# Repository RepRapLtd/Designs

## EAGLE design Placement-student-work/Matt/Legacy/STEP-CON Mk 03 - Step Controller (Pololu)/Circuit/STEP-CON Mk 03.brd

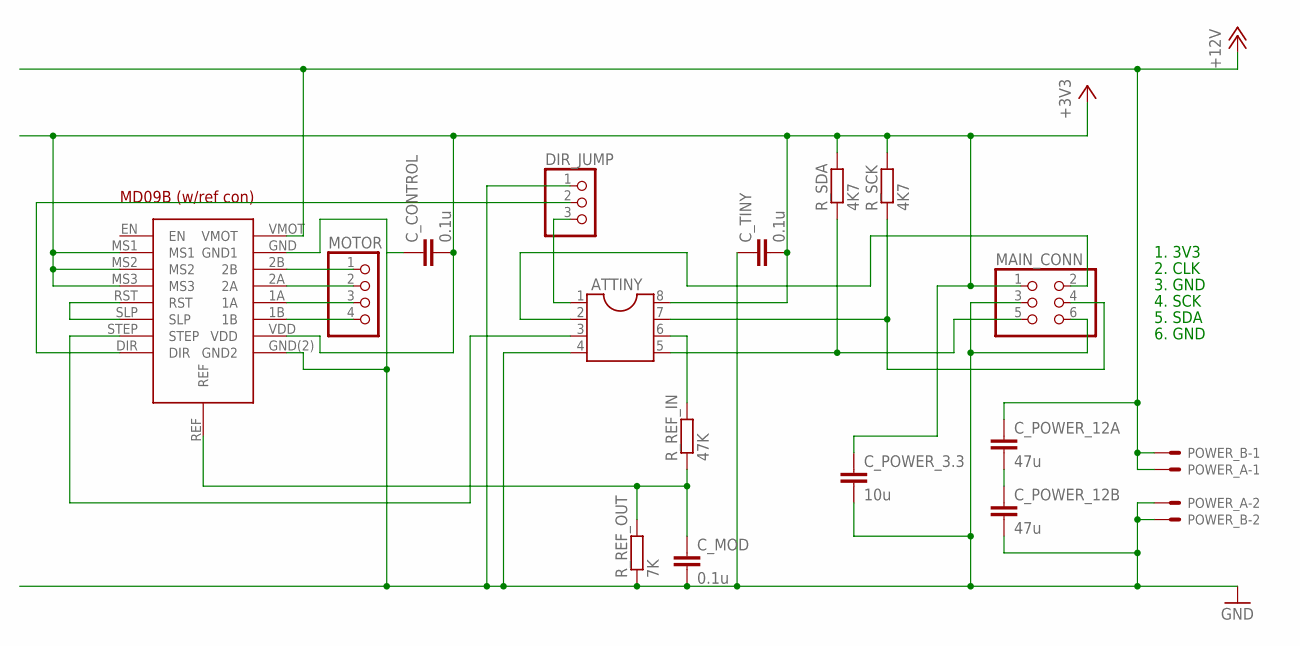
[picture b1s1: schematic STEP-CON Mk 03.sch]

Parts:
ATTINY: DIL8; DIL08
C_CONTROL: 0.1u; C1206
C_MOD: 0.1u; C1206
C_POWER_3.3: 10u; C1206
C_POWER_12A, C_POWER_12B: 47u; C1206
C_TINY: 0.1u; C1206
DIR_JUMP: PINHD-1X3; 1X03
MAIN_CONN: PINHD-2X3; 2X03
MOTOR: PINHD-1X4; 1X04
POWER_A: KK-156-2
POWER_B: KK-156-2
R_REF_IN: 47K; M0805
R_REF_OUT: 7K; M0805
R_SCK: 4K7; M0805
R_SDA: 4K7; M0805
U$1: MD09B_MOD_LP; MD90B_MOD_LP

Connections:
1A: MOTOR.3, U$1.1A
1B: MOTOR.4, U$1.1B
2A: MOTOR.2, U$1.2A
2B: MOTOR.1, U$1.2B
+3V3: ATTINY.8, C_CONTROL.2, C_POWER_3.3.1, C_TINY.2, MAIN_CONN.1, R_SCK.2, R_SDA.2, U$1.MS1, U$1.MS2, U$1.MS3, U$1.VDD
+12V: C_POWER_12A.1, POWER_A.1, POWER_B.1, U$1.VMOT
DIR: DIR_JUMP.2, U$1.DIR
GND: ATTINY.4, C_CONTROL.1, C_MOD.2, C_POWER_3.3.2, C_POWER_12B.2, C_TINY.1, DIR_JUMP.1, MAIN_CONN.3, MAIN_CONN.6, POWER_A.2, POWER_B.2, R_REF_OUT.1, U$1.GND (GND1), U$1.GND(2) (GND2)
unnamed: C_POWER_12A.2, C_POWER_12B.1
PWM: ATTINY.6, R_REF_IN.2
REF: C_MOD.1, R_REF_IN.1, R_REF_OUT.2, U$1.REF
RESET/DIR: ATTINY.1, DIR_JUMP.3
RST_SLP: U$1.RST, U$1.SLP
SCK: ATTINY.7, MAIN_CONN.4, R_SCK.1
SDA: ATTINY.5, MAIN_CONN.5, R_SDA.1
SKYCLOCK: ATTINY.2, MAIN_CONN.2
STEP: ATTINY.3, U$1.STEP

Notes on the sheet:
1. 3V3 2. CLK 3. GND 4. SCK 5. SDA 6. GND

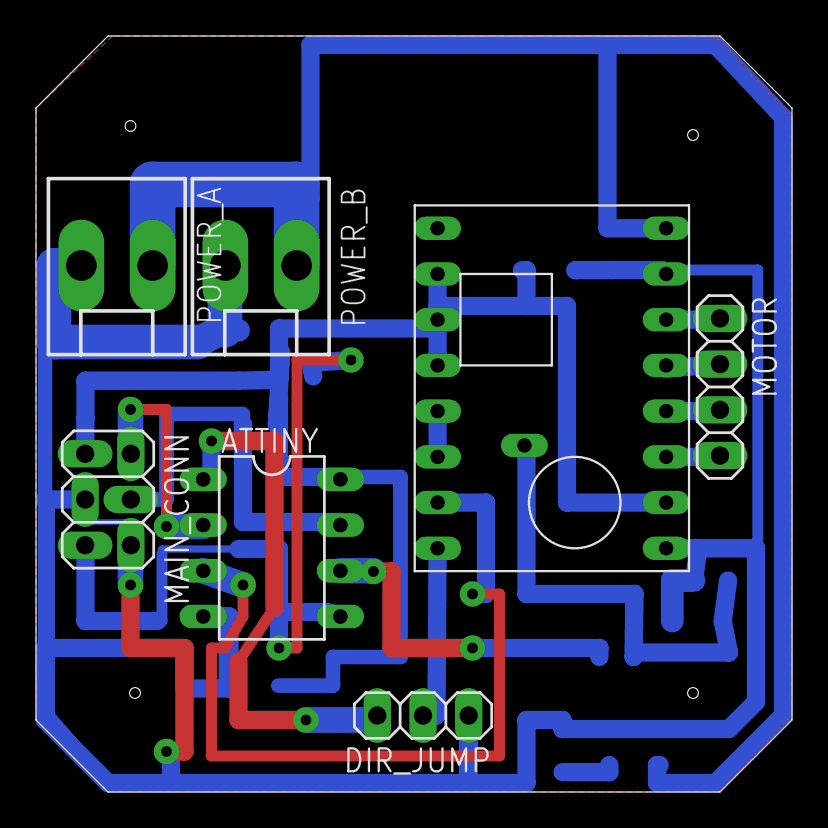
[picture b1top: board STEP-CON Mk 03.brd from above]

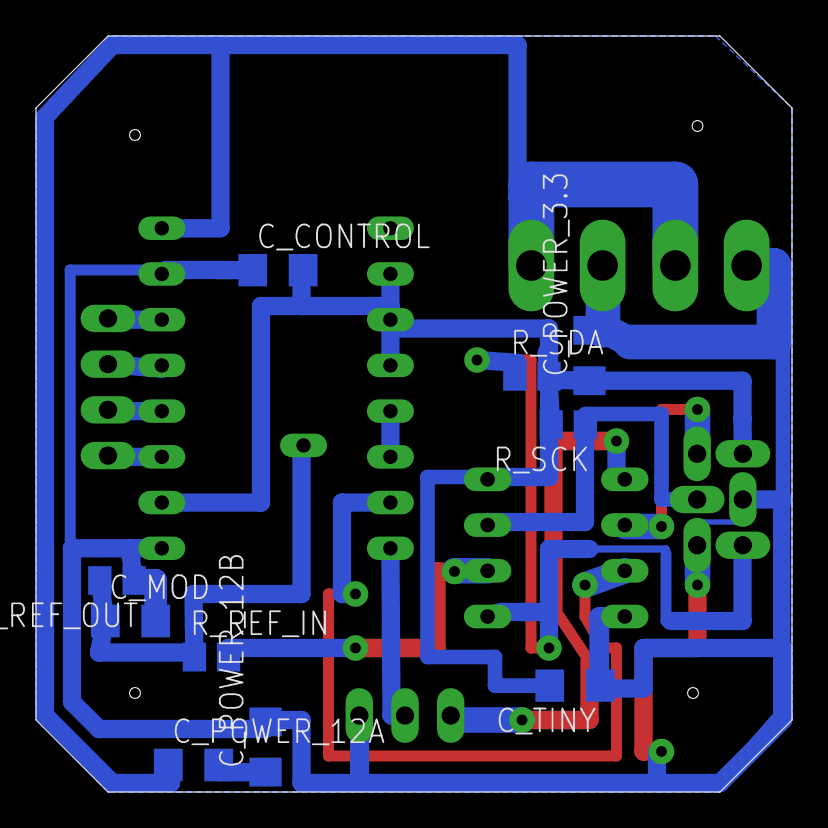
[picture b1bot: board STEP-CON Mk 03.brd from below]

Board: 2 copper layers, 42.0 x 42.0 mm, 17 parts (10 on the bottom side), 17 nets.

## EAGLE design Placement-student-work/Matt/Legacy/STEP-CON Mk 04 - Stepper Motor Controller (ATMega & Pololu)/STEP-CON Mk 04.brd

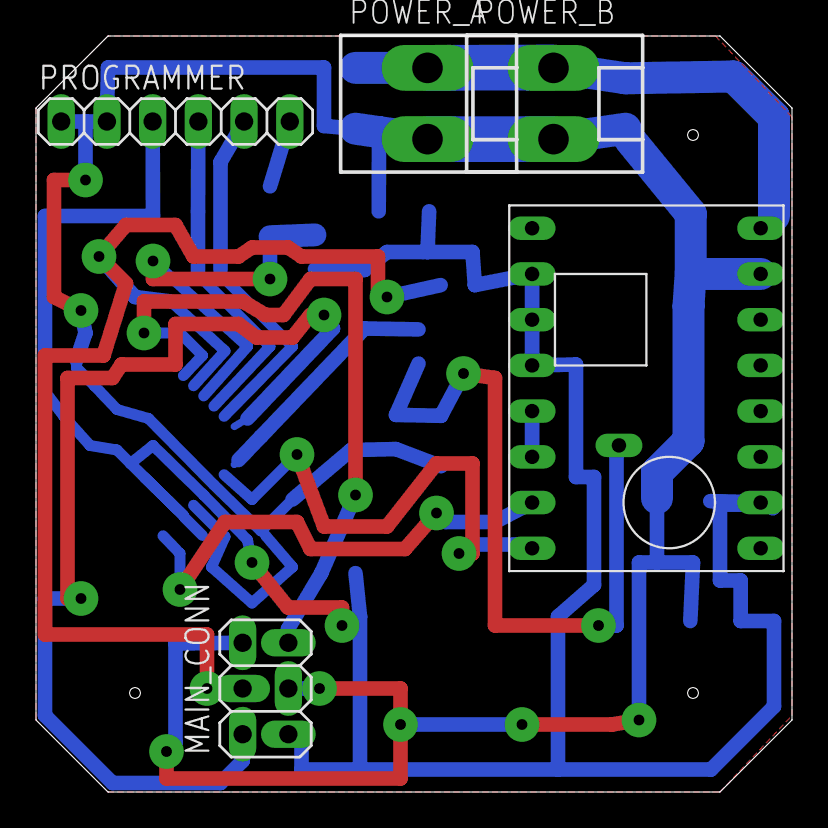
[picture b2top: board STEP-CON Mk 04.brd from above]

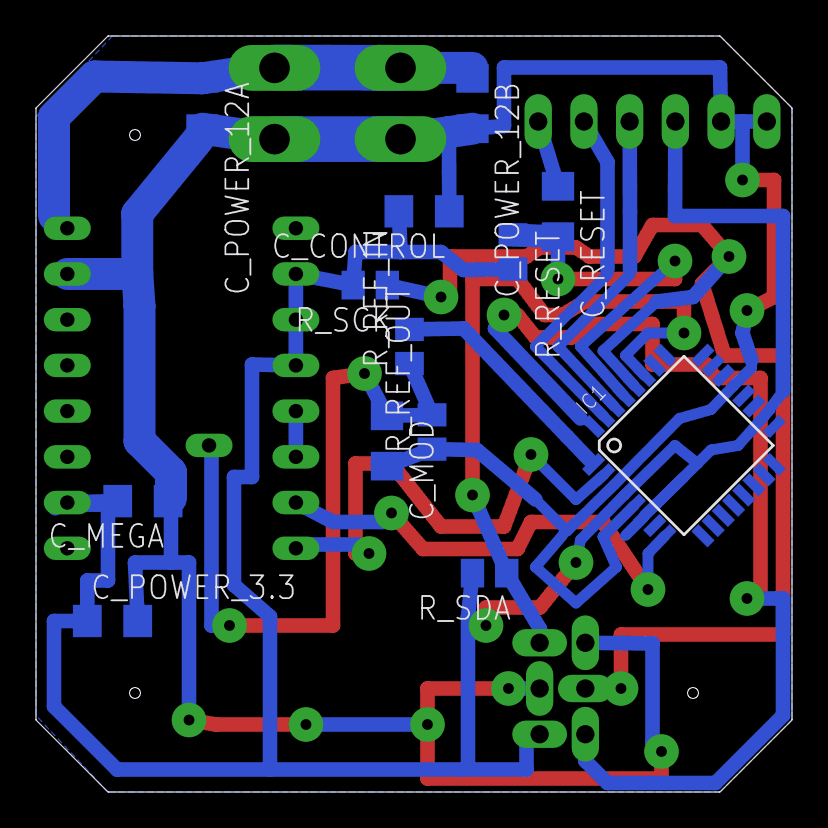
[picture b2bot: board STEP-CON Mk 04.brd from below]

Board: 2 copper layers, 42.0 x 42.0 mm, 18 parts (13 on the bottom side), 15 nets.

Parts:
C_CONTROL: 0.1u; C1206
C_MEGA: 0.1u; C1206
C_MOD: 0.1u; C1206
C_POWER_3.3: 10u; C1206
C_POWER_12A, C_POWER_12B: 47u; C1206
C_RESET: 0.1u; C1206
IC1: MEGA8-AI; TQFP32-08
MAIN_CONN: 2X03
POWER_A: KK-156-2
POWER_B: KK-156-2
PROGRAMMER: 1X06
R_REF_IN: 47K; M0805
R_REF_OUT: 7K; M0805
R_RESET: 4K7; M0805
R_SCK: 4K7; M0805
R_SDA: 4K7; M0805
U$1: MD09B_MOD_LP; MD90B_MOD_LP

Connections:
+3V3: C_CONTROL.2, C_MEGA.2, C_POWER_3.3.1, IC1.4, IC1.6, IC1.18, MAIN_CONN.1, PROGRAMMER.3, R_RESET.2, R_SCK.2, R_SDA.2, U$1.MS1, U$1.MS2, U$1.MS3, U$1.VDD
+12V: C_POWER_12A.1, C_POWER_12B.1, POWER_A.1, POWER_B.1, U$1.VMOT
DATA1: IC1.30, PROGRAMMER.4
DATA2: IC1.31, PROGRAMMER.5
DIR: IC1.2, U$1.DIR
GND: C_CONTROL.1, C_MEGA.1, C_MOD.2, C_POWER_3.3.2, C_POWER_12A.2, C_POWER_12B.2, IC1.3, IC1.5, IC1.21, MAIN_CONN.3, MAIN_CONN.6, POWER_A.2, POWER_B.2, PROGRAMMER.1, PROGRAMMER.2, R_REF_OUT.1, U$1.GND, U$1.GND(2)
PWM: IC1.1, R_REF_IN.2
REF: C_MOD.1, R_REF_IN.1, R_REF_OUT.2, U$1.REF
RESET: C_RESET.2, IC1.29, R_RESET.1
RESET_INPUT: C_RESET.1, PROGRAMMER.6
RST_SLP: U$1.RST, U$1.SLP
SCK: IC1.28, MAIN_CONN.4, R_SCK.1
SDA: IC1.27, MAIN_CONN.5, R_SDA.1
SKYCLOCK: IC1.32, MAIN_CONN.2
STEP: IC1.8, U$1.STEP

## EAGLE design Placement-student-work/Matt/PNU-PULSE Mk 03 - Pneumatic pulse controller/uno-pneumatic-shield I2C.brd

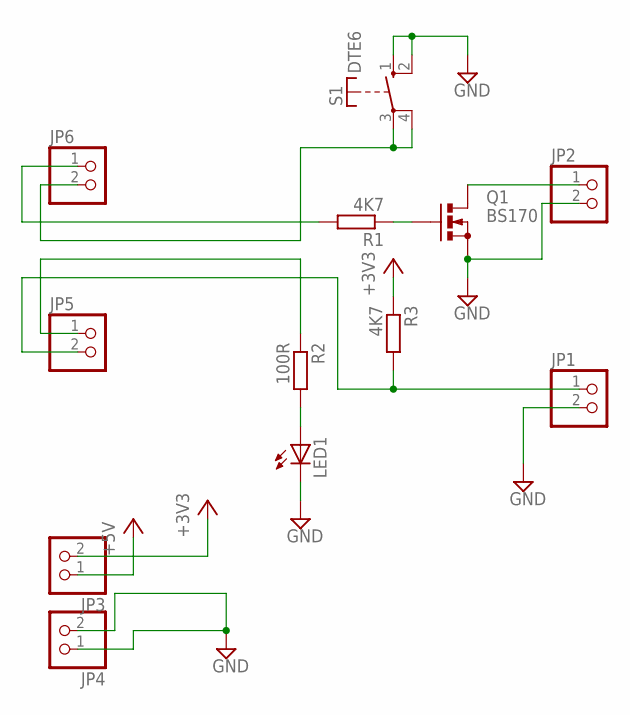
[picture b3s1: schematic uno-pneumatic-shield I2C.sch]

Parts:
JP1, JP2, JP3, JP4, JP5, JP6: PINHD-1X2; 1X02
LED1: LED3MM
Q1: BS170; SOT54E
R1, R3: 4K7; 0204/7
R2: 100R; 0204/7
S1: DTE6

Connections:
+3V3: JP3.2, R3.1
+5V: JP3.1
GND: JP1.2, JP2.2, JP4.1, JP4.2, LED1.K (C), Q1.S, S1.1 (S), S1.2 (S)
unnamed: JP6.1, R1.2
unnamed: Q1.G, R1.1
unnamed: LED1.A, R2.2
unnamed: JP2.1, Q1.D
unnamed: JP6.2, S1.3, S1.4
unnamed: JP1.1, JP5.2, R3.2
unnamed: JP5.1, R2.1

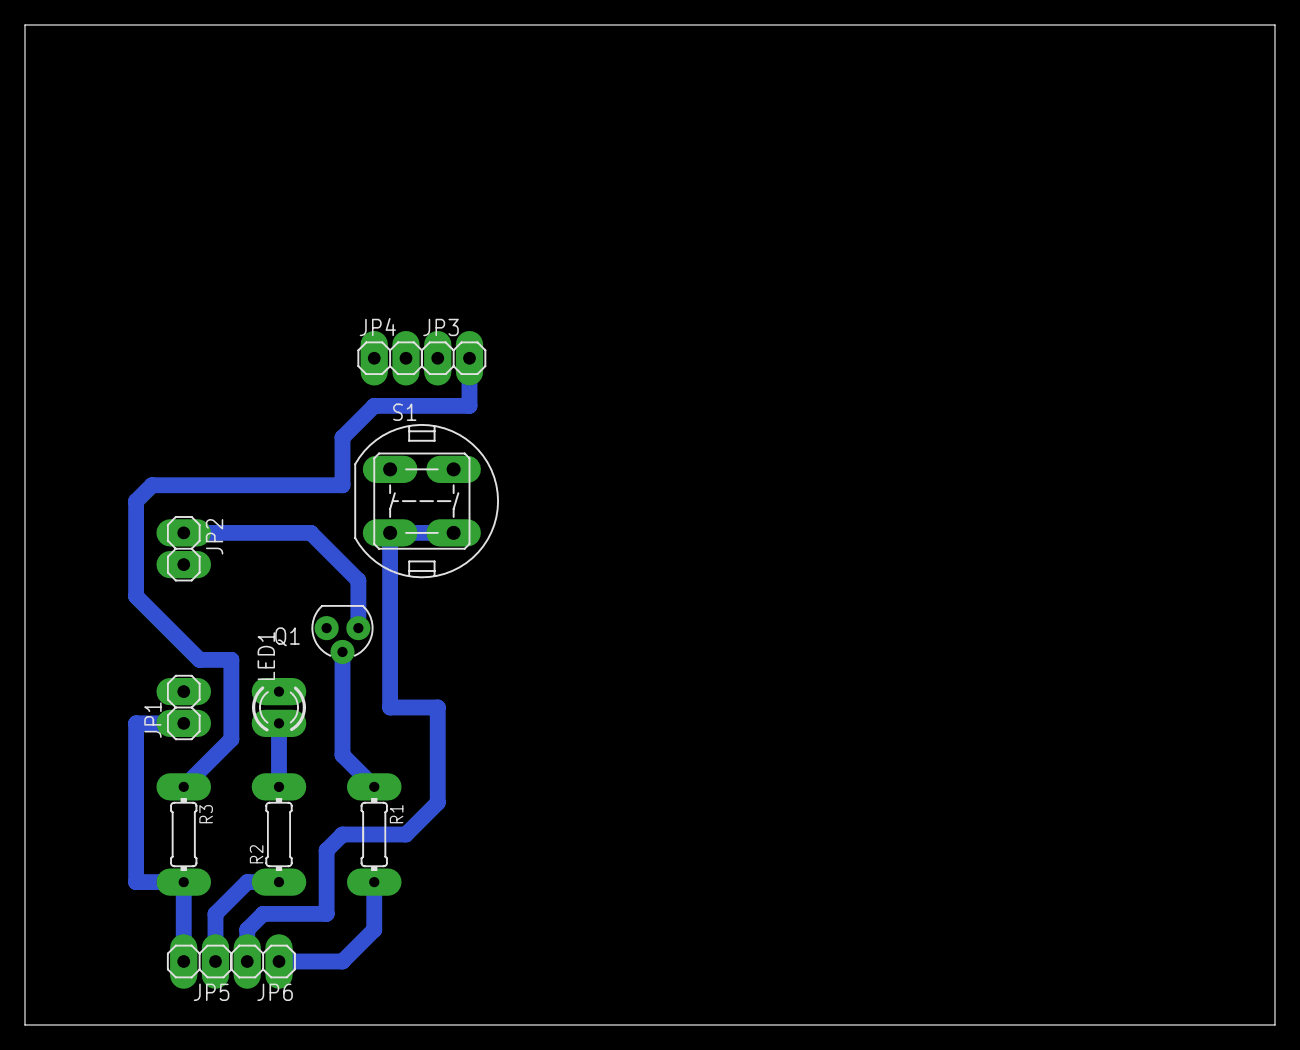
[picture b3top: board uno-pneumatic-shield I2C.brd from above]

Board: 2 copper layers, 100.0 x 80.0 mm, 12 parts (0 on the bottom side), 9 nets.

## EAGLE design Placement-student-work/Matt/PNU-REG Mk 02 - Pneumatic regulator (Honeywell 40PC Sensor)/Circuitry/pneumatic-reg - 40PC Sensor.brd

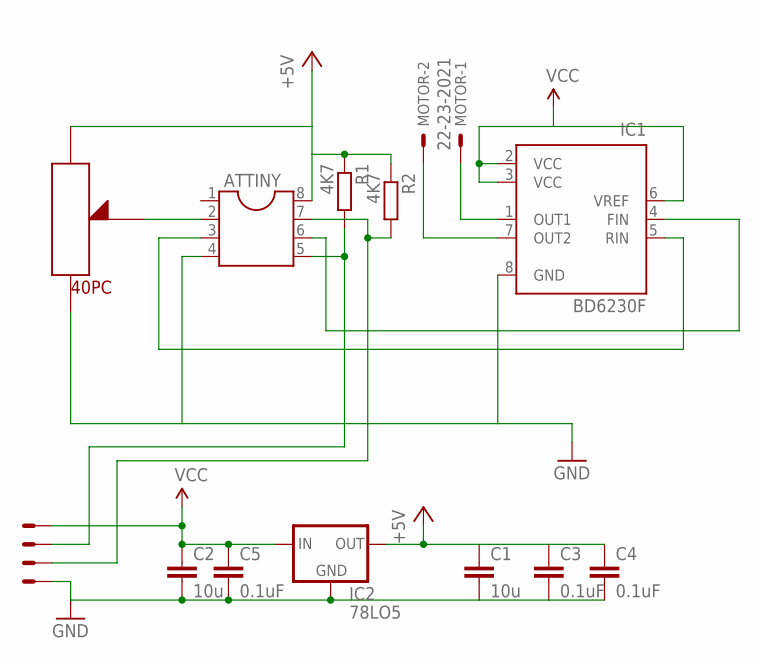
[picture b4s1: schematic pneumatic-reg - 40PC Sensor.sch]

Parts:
ATTINY: DIL8; DIL08
C1, C2: 10u; C1206
C3, C4, C5: 0.1uF; C1206
IC1: BD6230F; SOP8
IC2: 78LO5; 78LXX
MOTOR: 22-23-2021
R1, R2: 4K7; M0805
U$1: 40PC
X2: 22-23-2041

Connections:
+5V: ATTINY.8, C1.1, C3.1, C4.1, IC2.OUT, R1.1, R2.1, U$1.PIN1
D0: ATTINY.3, IC1.5 (RIN)
D1: ATTINY.6, IC1.4 (FIN)
GND: ATTINY.4, C1.2, C2.2, C3.2, C4.2, C5.2, IC1.8 (GND), IC2.GND, U$1.PIN2, X2.1
unnamed: ATTINY.2, U$1.PIN3
unnamed: ATTINY.5, R1.2, X2.3
unnamed: IC1.7 (OUT2), MOTOR.2
unnamed: IC1.1 (OUT1), MOTOR.1
unnamed: ATTINY.7, R2.2, X2.2
VCC: C2.1, C5.1, IC1.2 (VCC), IC1.3 (VCC), IC1.6 (VREF), IC2.IN, X2.4

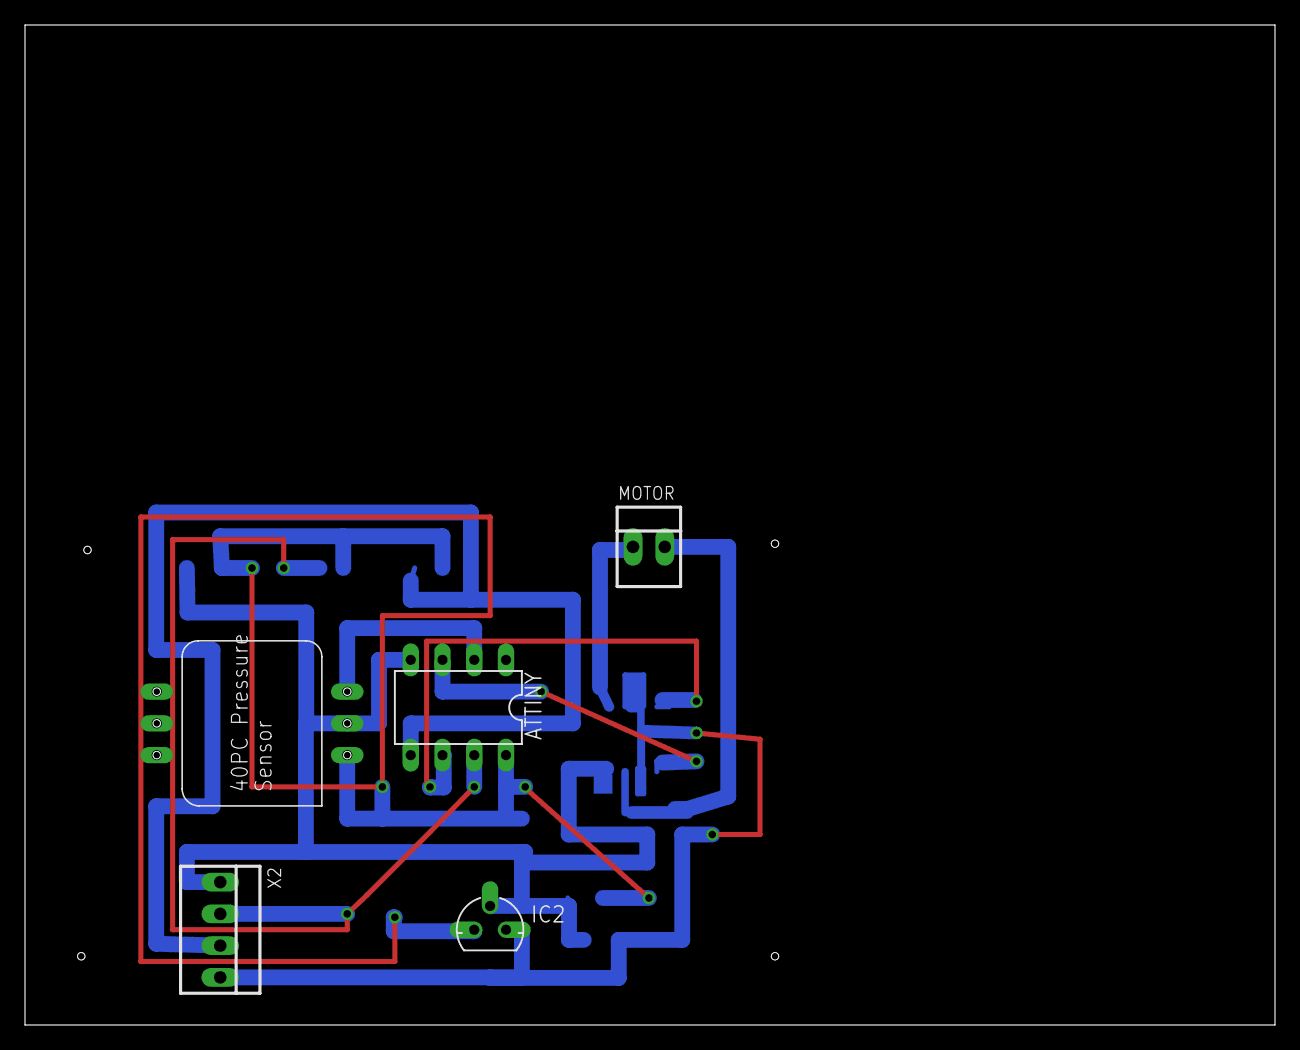
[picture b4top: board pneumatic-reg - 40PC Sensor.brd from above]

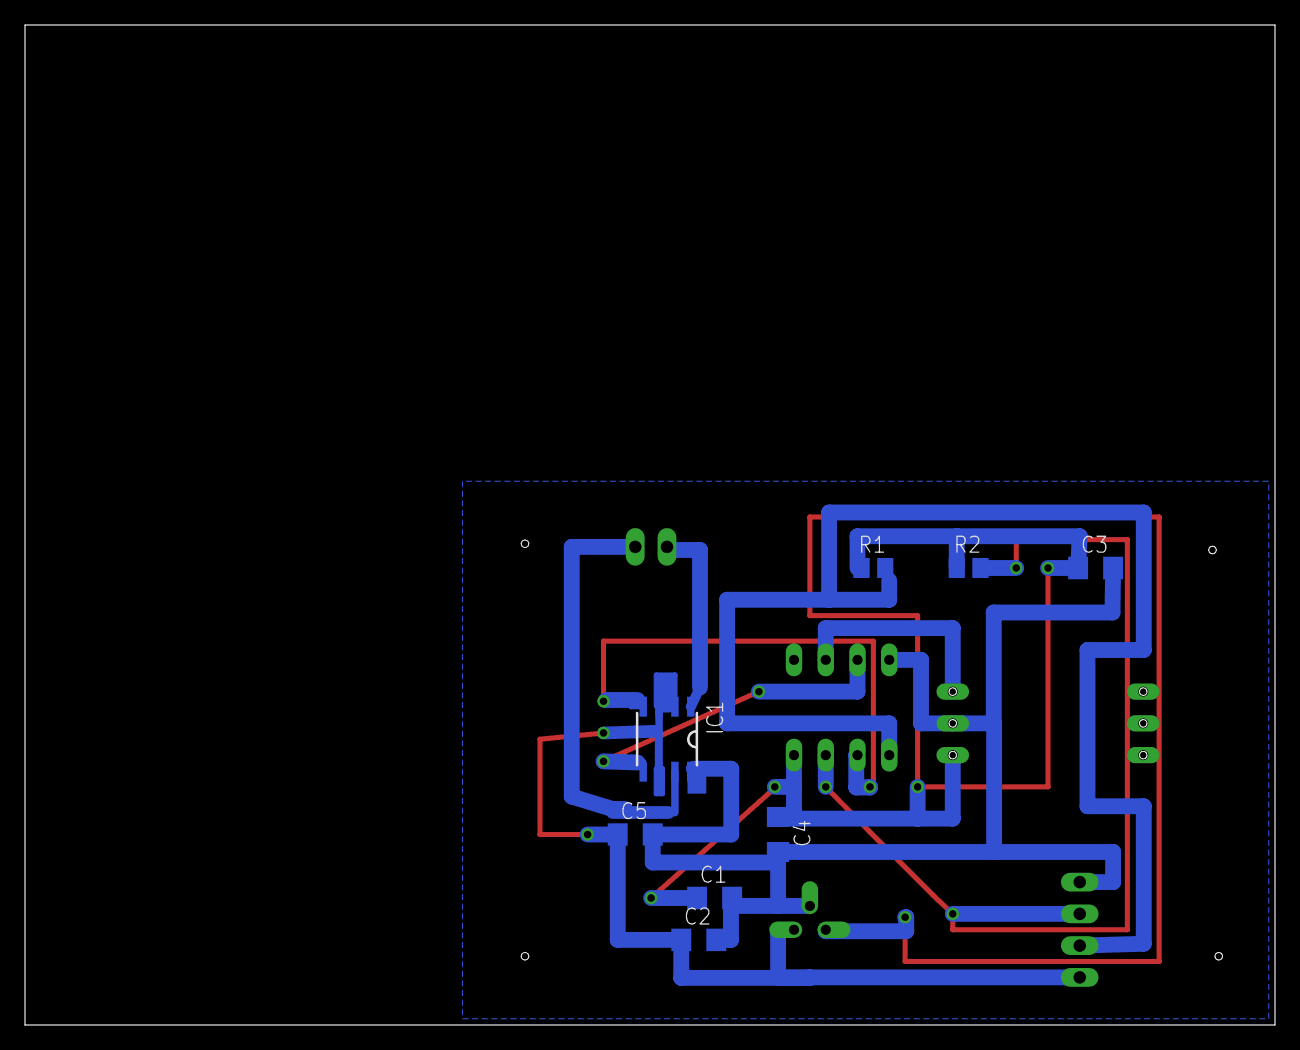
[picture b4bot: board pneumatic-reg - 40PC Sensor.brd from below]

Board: 2 copper layers, 100.0 x 80.0 mm, 13 parts (8 on the bottom side), 10 nets.

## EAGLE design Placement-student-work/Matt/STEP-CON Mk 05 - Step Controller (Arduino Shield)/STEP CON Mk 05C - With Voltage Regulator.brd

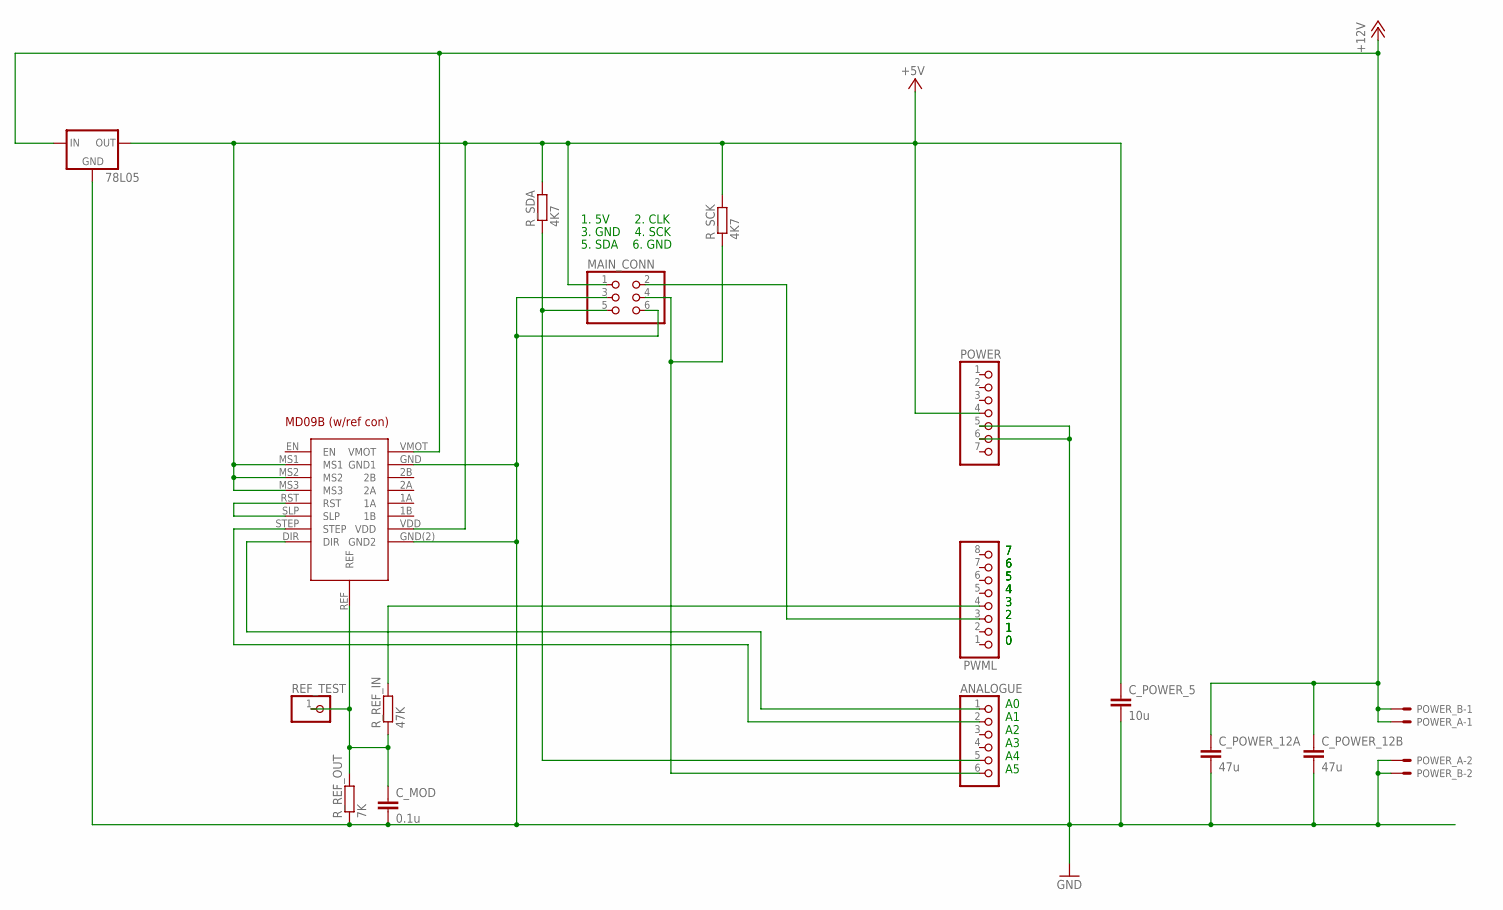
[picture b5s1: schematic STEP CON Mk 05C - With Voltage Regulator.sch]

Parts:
78L05: 78LXX
ANALOGUE: PINHD-1X6; 1X06
C_MOD: 0.1u; C1206
C_POWER_5: 10u; C1206
C_POWER_12A, C_POWER_12B: 47u; C1206
MAIN_CONN: PINHD-2X3; 2X03
POWER: PINHD-1X7; 1X07
POWER_A: KK-156-2
POWER_B: KK-156-2
PWML: PINHD-1X8; 1X08
REF_TEST: PINHD-1X1; 1X01
R_REF_IN: 47K; M0805
R_REF_OUT: 7K; M0805
R_SCK: 4K7; M0805
R_SDA: 4K7; M0805
U$1: MD09B_MOD_LP; MD90B_MOD_LP

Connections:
+5V: 78L05.OUT, C_POWER_5.1, MAIN_CONN.1, POWER.4, R_SCK.2, R_SDA.2, U$1.MS1, U$1.MS2, U$1.MS3, U$1.VDD
+12V: 78L05.IN, C_POWER_12A.1, C_POWER_12B.1, POWER_A.1, POWER_B.1, U$1.VMOT
DIR: ANALOGUE.1, U$1.DIR
GND: 78L05.GND, C_MOD.2, C_POWER_5.2, C_POWER_12A.2, C_POWER_12B.2, MAIN_CONN.3, MAIN_CONN.6, POWER.5, POWER.6, POWER_A.2, POWER_B.2, R_REF_OUT.1, U$1.GND (GND1), U$1.GND(2) (GND2)
PWM: PWML.4, R_REF_IN.2
REF1: C_MOD.1, REF_TEST.1, R_REF_IN.1, R_REF_OUT.2, U$1.REF
SCK: ANALOGUE.6, MAIN_CONN.4, R_SCK.1
SDA: ANALOGUE.5, MAIN_CONN.5, R_SDA.1
SKYCLOCK: MAIN_CONN.2, PWML.3
SLP-RST: U$1.RST, U$1.SLP
STEP: ANALOGUE.2, U$1.STEP

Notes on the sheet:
1. 5V 2. CLK 3. GND 4. SCK 5. SDA 6. GND
A0 A1 A2 A3 A4 A5

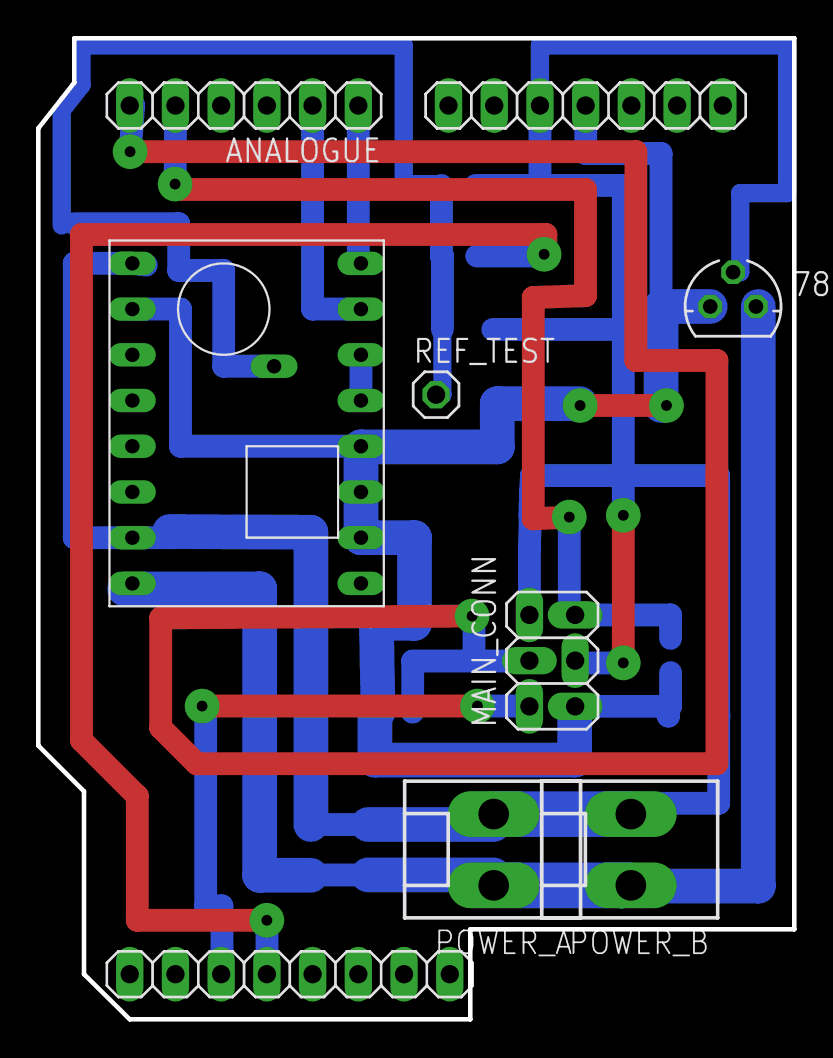
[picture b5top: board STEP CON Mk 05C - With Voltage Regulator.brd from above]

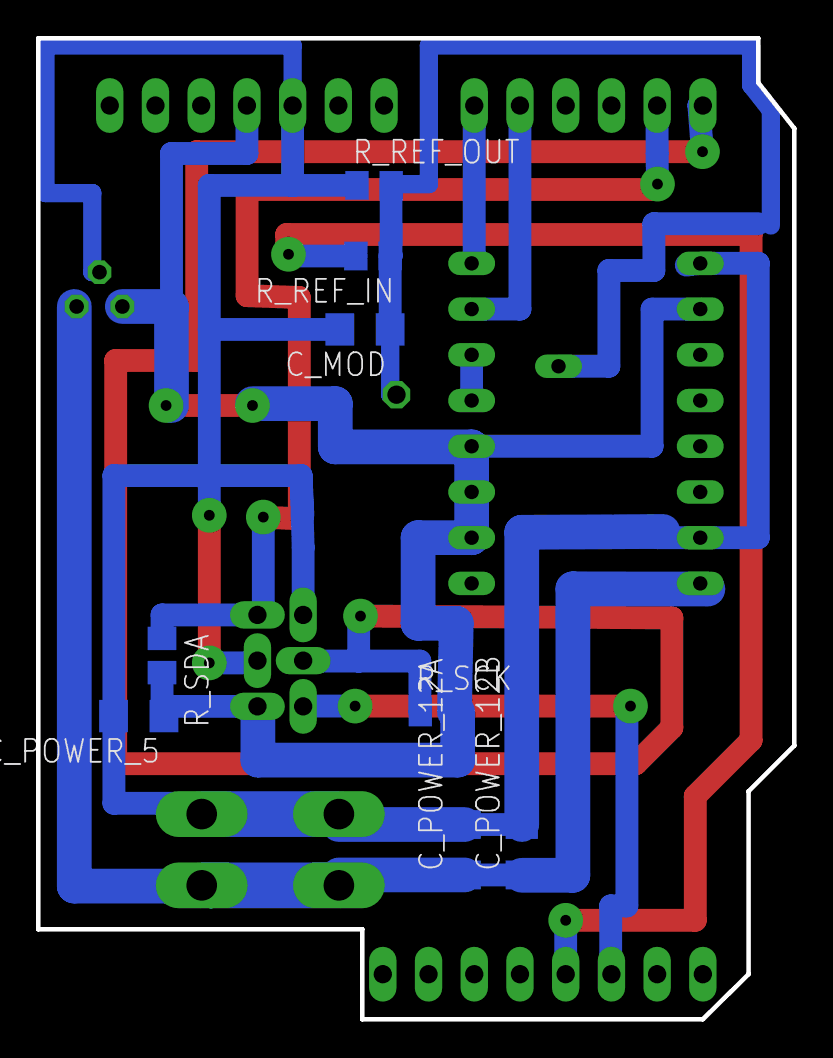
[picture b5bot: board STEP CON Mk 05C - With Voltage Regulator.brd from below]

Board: 2 copper layers, 42.0 x 54.5 mm, 17 parts (8 on the bottom side), 11 nets.

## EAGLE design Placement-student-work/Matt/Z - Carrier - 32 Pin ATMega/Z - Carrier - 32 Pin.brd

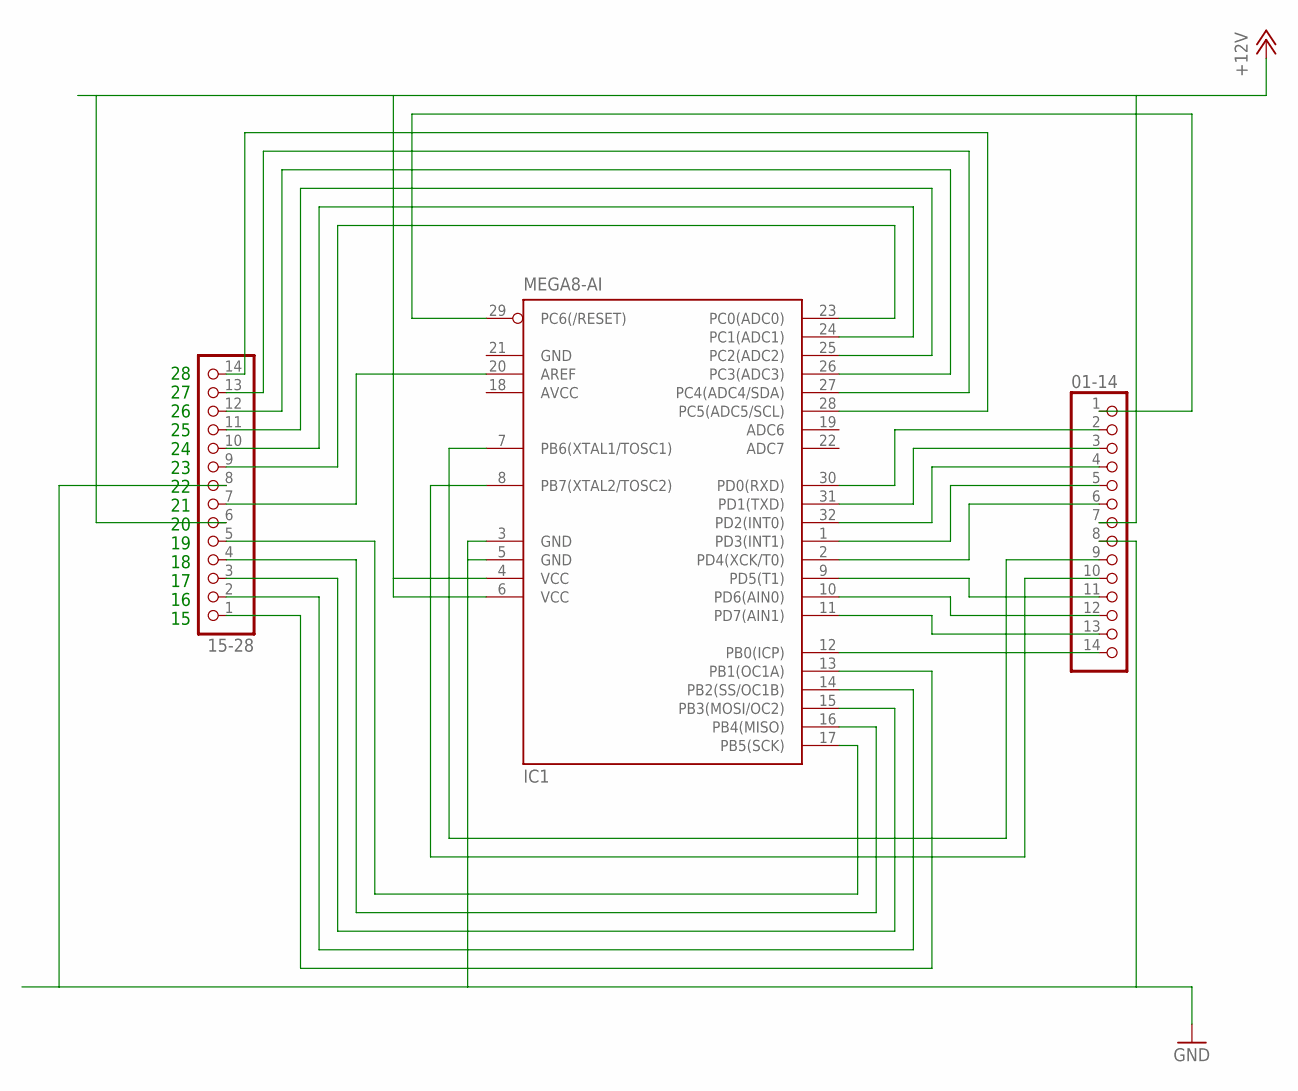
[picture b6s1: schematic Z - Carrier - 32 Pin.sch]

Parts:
01-14, 15-28: PINHD-1X14; 1X14
IC1: MEGA8-AI; TQFP32-08

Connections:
1: 01-14.1, IC1.29 (PC6(/RESET))
14: 01-14.14, IC1.12 (PB0(ICP))
15: 15-28.1, IC1.13 (PB1(OC1A))
28: 15-28.14, IC1.28 (PC5(ADC5/SCL))
+12V: 01-14.7, 15-28.6, IC1.4 (VCC), IC1.6 (VCC)
AVCC: IC1.18 (AVCC)
GND: 01-14.8, 15-28.8, IC1.3 (GND), IC1.5 (GND), IC1.21 (GND)
unnamed: 01-14.2, IC1.30 (PD0(RXD))
unnamed: 01-14.3, IC1.31 (PD1(TXD))
unnamed: 01-14.4, IC1.32 (PD2(INT0))
unnamed: 01-14.5, IC1.1 (PD3(INT1))
unnamed: 01-14.6, IC1.2 (PD4(XCK/T0))
unnamed: 01-14.9, IC1.7 (PB6(XTAL1/TOSC1))
unnamed: 01-14.10, IC1.8 (PB7(XTAL2/TOSC2))
unnamed: 01-14.11, IC1.9 (PD5(T1))
unnamed: 01-14.12, IC1.10 (PD6(AIN0))
unnamed: 01-14.13, IC1.11 (PD7(AIN1))
unnamed: 15-28.2, IC1.14 (PB2(SS/OC1B))
unnamed: 15-28.3, IC1.15 (PB3(MOSI/OC2))
unnamed: 15-28.4, IC1.16 (PB4(MISO))
unnamed: 15-28.5, IC1.17 (PB5(SCK))
unnamed: 15-28.7, IC1.20 (AREF)
unnamed: 15-28.9, IC1.23 (PC0(ADC0))
unnamed: 15-28.10, IC1.24 (PC1(ADC1))
unnamed: 15-28.11, IC1.25 (PC2(ADC2))
unnamed: 15-28.12, IC1.26 (PC3(ADC3))
unnamed: 15-28.13, IC1.27 (PC4(ADC4/SDA))

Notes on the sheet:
28 27 26 25 24 23 22 21 20 19 18 17 16 15

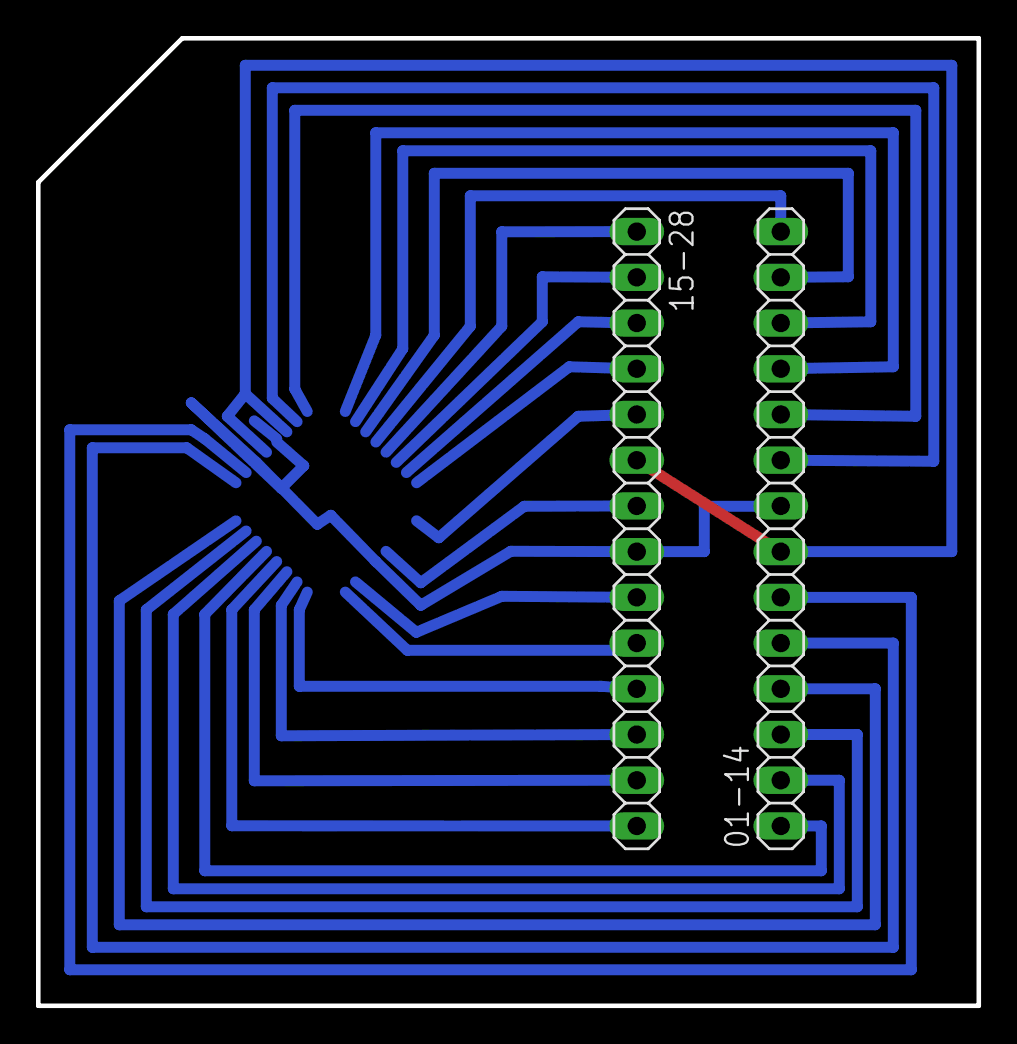
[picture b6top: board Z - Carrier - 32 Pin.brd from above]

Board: 2 copper layers, 52.2 x 53.8 mm, 3 parts (1 on the bottom side), 26 nets.

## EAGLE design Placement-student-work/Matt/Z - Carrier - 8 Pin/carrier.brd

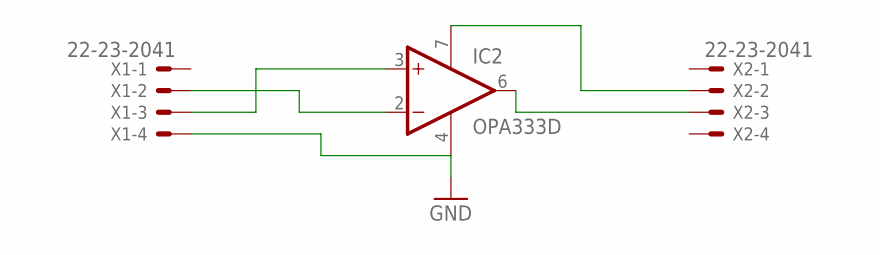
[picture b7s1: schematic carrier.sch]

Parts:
IC2: OPA333D; SO08
X1, X2: 22-23-2041

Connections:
GND: IC2.4 (V-), X1.4
unnamed: IC2.2 (-IN), X1.2
unnamed: IC2.3 (+IN), X1.3
unnamed: IC2.6 (OUT), X2.3
unnamed: IC2.7 (V+), X2.2

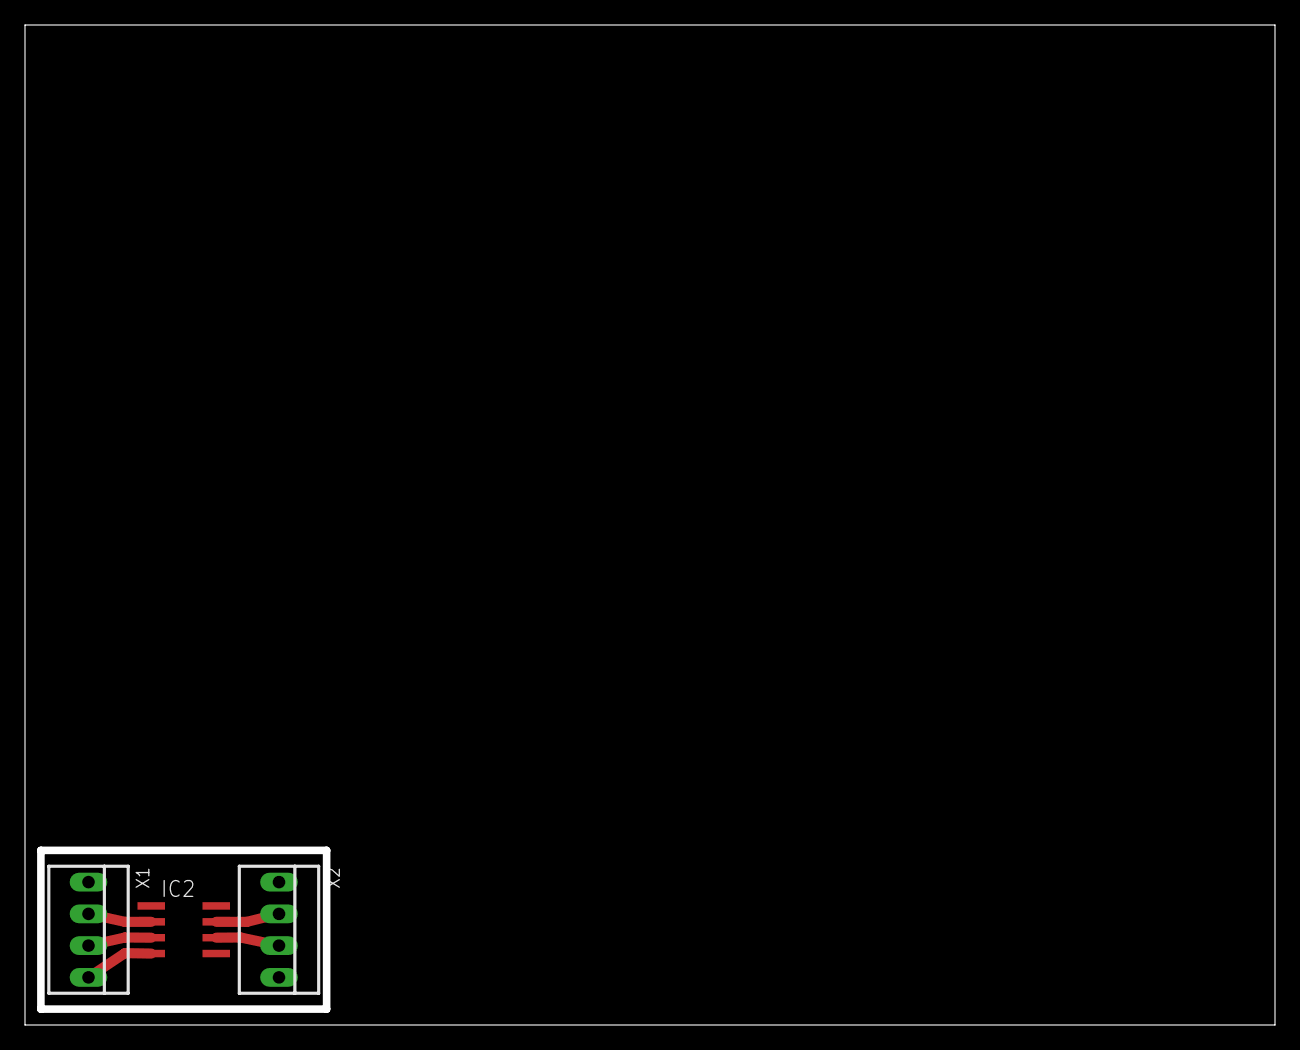
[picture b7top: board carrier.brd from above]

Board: 2 copper layers, 100.0 x 80.0 mm, 3 parts (0 on the bottom side), 5 nets.

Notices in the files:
parts and their libraries:
SparkFun: Licensing: CC v3.0 Share-Alike You are welcome to use this library for commercial purposes.
